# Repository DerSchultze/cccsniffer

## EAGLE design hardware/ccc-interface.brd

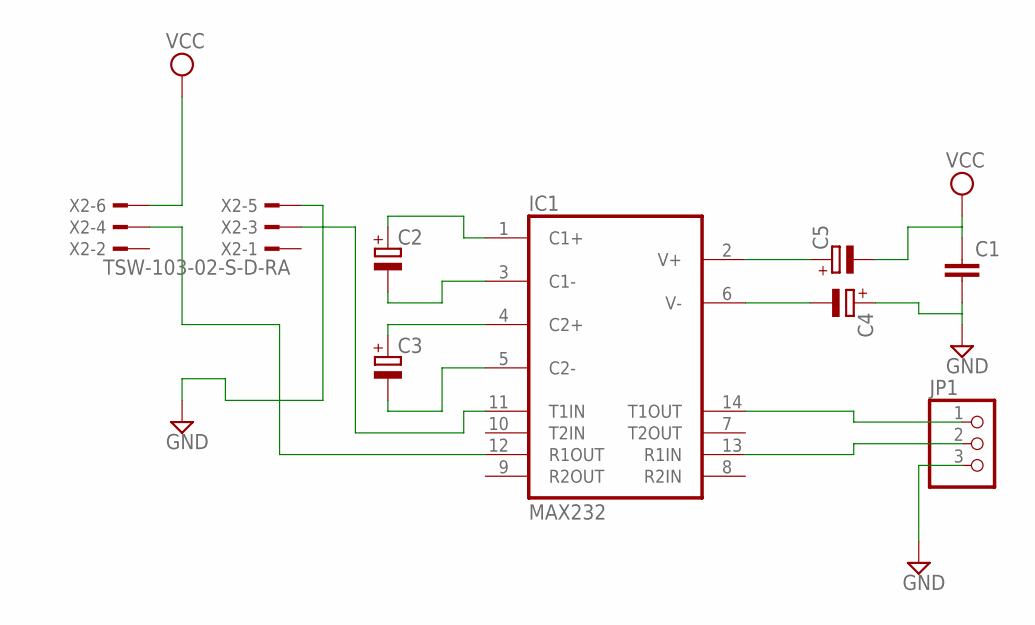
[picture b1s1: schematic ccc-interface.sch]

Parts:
C1: C-EU050-024X044; C050-024X044
C2, C3, C4, C5: CPOL-EUE1.8-4; E1,8-4
IC1: MAX232; DIL16
JP1: PINHD-1X3/90; 1X03/90
X2: TSW-103-02-S-D-RA

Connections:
GND: C1.2, C4.+, IC1.15 (GND), JP1.3, X2.5
unnamed: C2.+, IC1.1 (C1+)
unnamed: C2.-, IC1.3 (C1-)
unnamed: C5.+, IC1.2 (V+)
unnamed: C4.-, IC1.6 (V-)
unnamed: C3.+, IC1.4 (C2+)
unnamed: C3.-, IC1.5 (C2-)
unnamed: IC1.13 (R1IN), JP1.2
unnamed: IC1.14 (T1OUT), JP1.1
unnamed: IC1.11 (T1IN), X2.3
unnamed: IC1.12 (R1OUT), X2.4
VCC: C1.1, C5.-, IC1.16 (VCC), X2.6

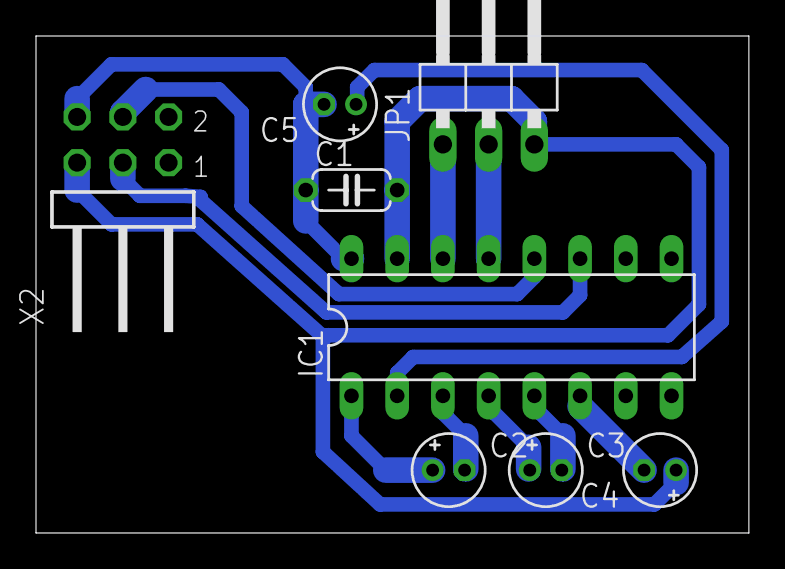
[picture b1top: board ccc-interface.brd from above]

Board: 2 copper layers, 39.6 x 27.6 mm, 8 parts (0 on the bottom side), 12 nets.

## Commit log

2020-01-23 Add hardware
